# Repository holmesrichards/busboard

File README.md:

Eurorack/Kosmo Busboards
========================

* [busboard](busboard): A Eurorack power bus board in Kicad.
Size 31.5 x 200 mm.
* [busboard10](busboard10): 2x5 pin connector ±12V adaptation.
Size 25 x 200 mm.

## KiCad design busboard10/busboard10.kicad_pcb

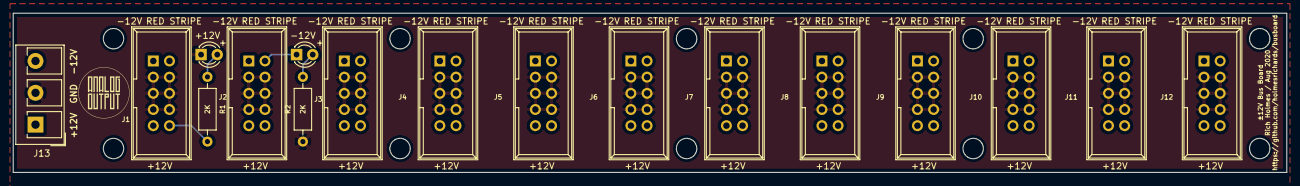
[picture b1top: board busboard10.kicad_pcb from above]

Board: 2 copper layers, 200.0 x 25.0 mm, 17 parts (0 on the bottom side), 5 nets.

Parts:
+12v1: LED; LED_D3.0mm
-12v1: LED; LED_D3.0mm
J1, J2, J3, J4, J5, J6, J7, J8, J9, J10, J11, J12: Synth_power_2x5_narrow; Power_Header
J13: Conn_01x03; TerminalBlock_Degson_DG301_1x03_P5.00mm_Vertical
R1, R2: 2K; R_Axial_DIN0207_L6.3mm_D2.5mm_P10.16mm_Horizontal

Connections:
+12V: J1.9, J1.10, J2.9, J2.10, J3.9, J3.10, J4.9, J4.10, J5.9, J5.10, J6.9, J6.10, J7.9, J7.10, J8.9, J8.10, J9.9, J9.10, J10.9, J10.10, J11.9, J11.10, J12.9, J12.10, J13.1, R1.2
-12V: -12v1.1, J1.1, J1.2, J2.1, J2.2, J3.1, J3.2, J4.1, J4.2, J5.1, J5.2, J6.1, J6.2, J7.1, J7.2, J8.1, J8.2, J9.1, J9.2, J10.1, J10.2, J11.1, J11.2, J12.1, J12.2, J13.3
GND: +12v1.1, J1.3, J1.4, J1.5, J1.6, J1.7, J1.8, J2.3, J2.4, J2.5, J2.6, J2.7, J2.8, J3.3, J3.4, J3.5, J3.6, J3.7, J3.8, J4.3, J4.4, J4.5, J4.6, J4.7, J4.8, J5.3, J5.4, J5.5, J5.6, J5.7, J5.8, J6.3, J6.4, J6.5, J6.6, J6.7, J6.8, J7.3, J7.4, J7.5, J7.6, J7.7, J7.8, J8.3, J8.4, J8.5, J8.6, J8.7, J8.8, J9.3, J9.4, J9.5, J9.6, J9.7, J9.8, J10.3, J10.4, J10.5, J10.6, J10.7, J10.8, J11.3, J11.4, J11.5, J11.6, J11.7, J11.8, J12.3, J12.4, J12.5, J12.6, J12.7, J12.8, J13.2, R2.1
unnamed: +12v1.2, R1.1
unnamed: -12v1.2, R2.2

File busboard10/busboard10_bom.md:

# busboard10 BOM

Sun 02 Aug 2020 11:37:44 AM EDT

Generated from schematic by Eeschema 5.1.6-c6e7f7d~86~ubuntu18.04.1

**Component Count:** 17

| Value | Qty | Part | Description | Vendor |
| ----- | --- | ---- | ----------- | ------ |
| +12v1, -12v1 | 2 | LED | Light emitting diode | Tayda A-261 |
| J1, J2, J3, J4, J5, J6, J7, J8, J9, J10, J11, J12 | 12 | Synth_power_2x5_narrow | 2x5 IDC connector (Eurorack style power header) | Tayda A-2939 |
| J13 | 1 | Conn_01x03 | 3 position terminal block (5 mm pitch) | Tayda A-669 |
| R1, R2 | 2 | 2K | Resistor | Tayda A-2307 |

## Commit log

2020-08-02 First version after fork, adds busboard10
2020-08-02 anal centering
2020-08-02 update schematic
2020-08-02 correct dimension
2020-08-02 fill
2020-08-02 mounting holes
2020-08-02 mounting holes fill
2020-08-02 not not tested
2020-08-02 page settings
2020-08-02 Tayda part numbers
2020-08-05 Gerbers
2020-08-17 Correct orientation of terminal block
2020-08-17 Update PNG
2021-01-02 Footprints updated
2021-01-17 Include lib table files
2021-02-19 Footprint update
2021-02-28 Update .gitignore, DIN5
2021-05-08 Changed resistor footprint
